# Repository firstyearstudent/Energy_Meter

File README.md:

<<<<<<< HEAD
# Energy_Meter
=======
# _Sample project_

(See the README.md file in the upper level 'examples' directory for more information about examples.)

This is the simplest buildable example. The example is used by command `idf.py create-project`
that copies the project to user specified path and set it's name. For more information follow the [docs page](https://docs.espressif.com/projects/esp-idf/en/latest/api-guides/build-system.html#start-a-new-project)

## How to use example
We encourage the users to use the example as a template for the new projects.
A recommended way is to follow the instructions on a [docs page](https://docs.espressif.com/projects/esp-idf/en/latest/api-guides/build-system.html#start-a-new-project).

## Example folder contents

The project **sample_project** contains one source file in C language [main.c](main/main.c). The file is located in folder [main](main).

ESP-IDF projects are built using CMake. The project build configuration is contained in `CMakeLists.txt`
files that provide set of directives and instructions describing the project's source files and targets
(executable, library, or both). 

Below is short explanation of remaining files in the project folder.

```
├── CMakeLists.txt
├── main
│   ├── CMakeLists.txt
│   └── main.c
└── README.md                  This is the file you are currently reading
```
Additionally, the sample project contains Makefile and component.mk files, used for the legacy Make based build system. 
They are not used or needed when building with CMake and idf.py.
>>>>>>> 912d5ab (first commit)

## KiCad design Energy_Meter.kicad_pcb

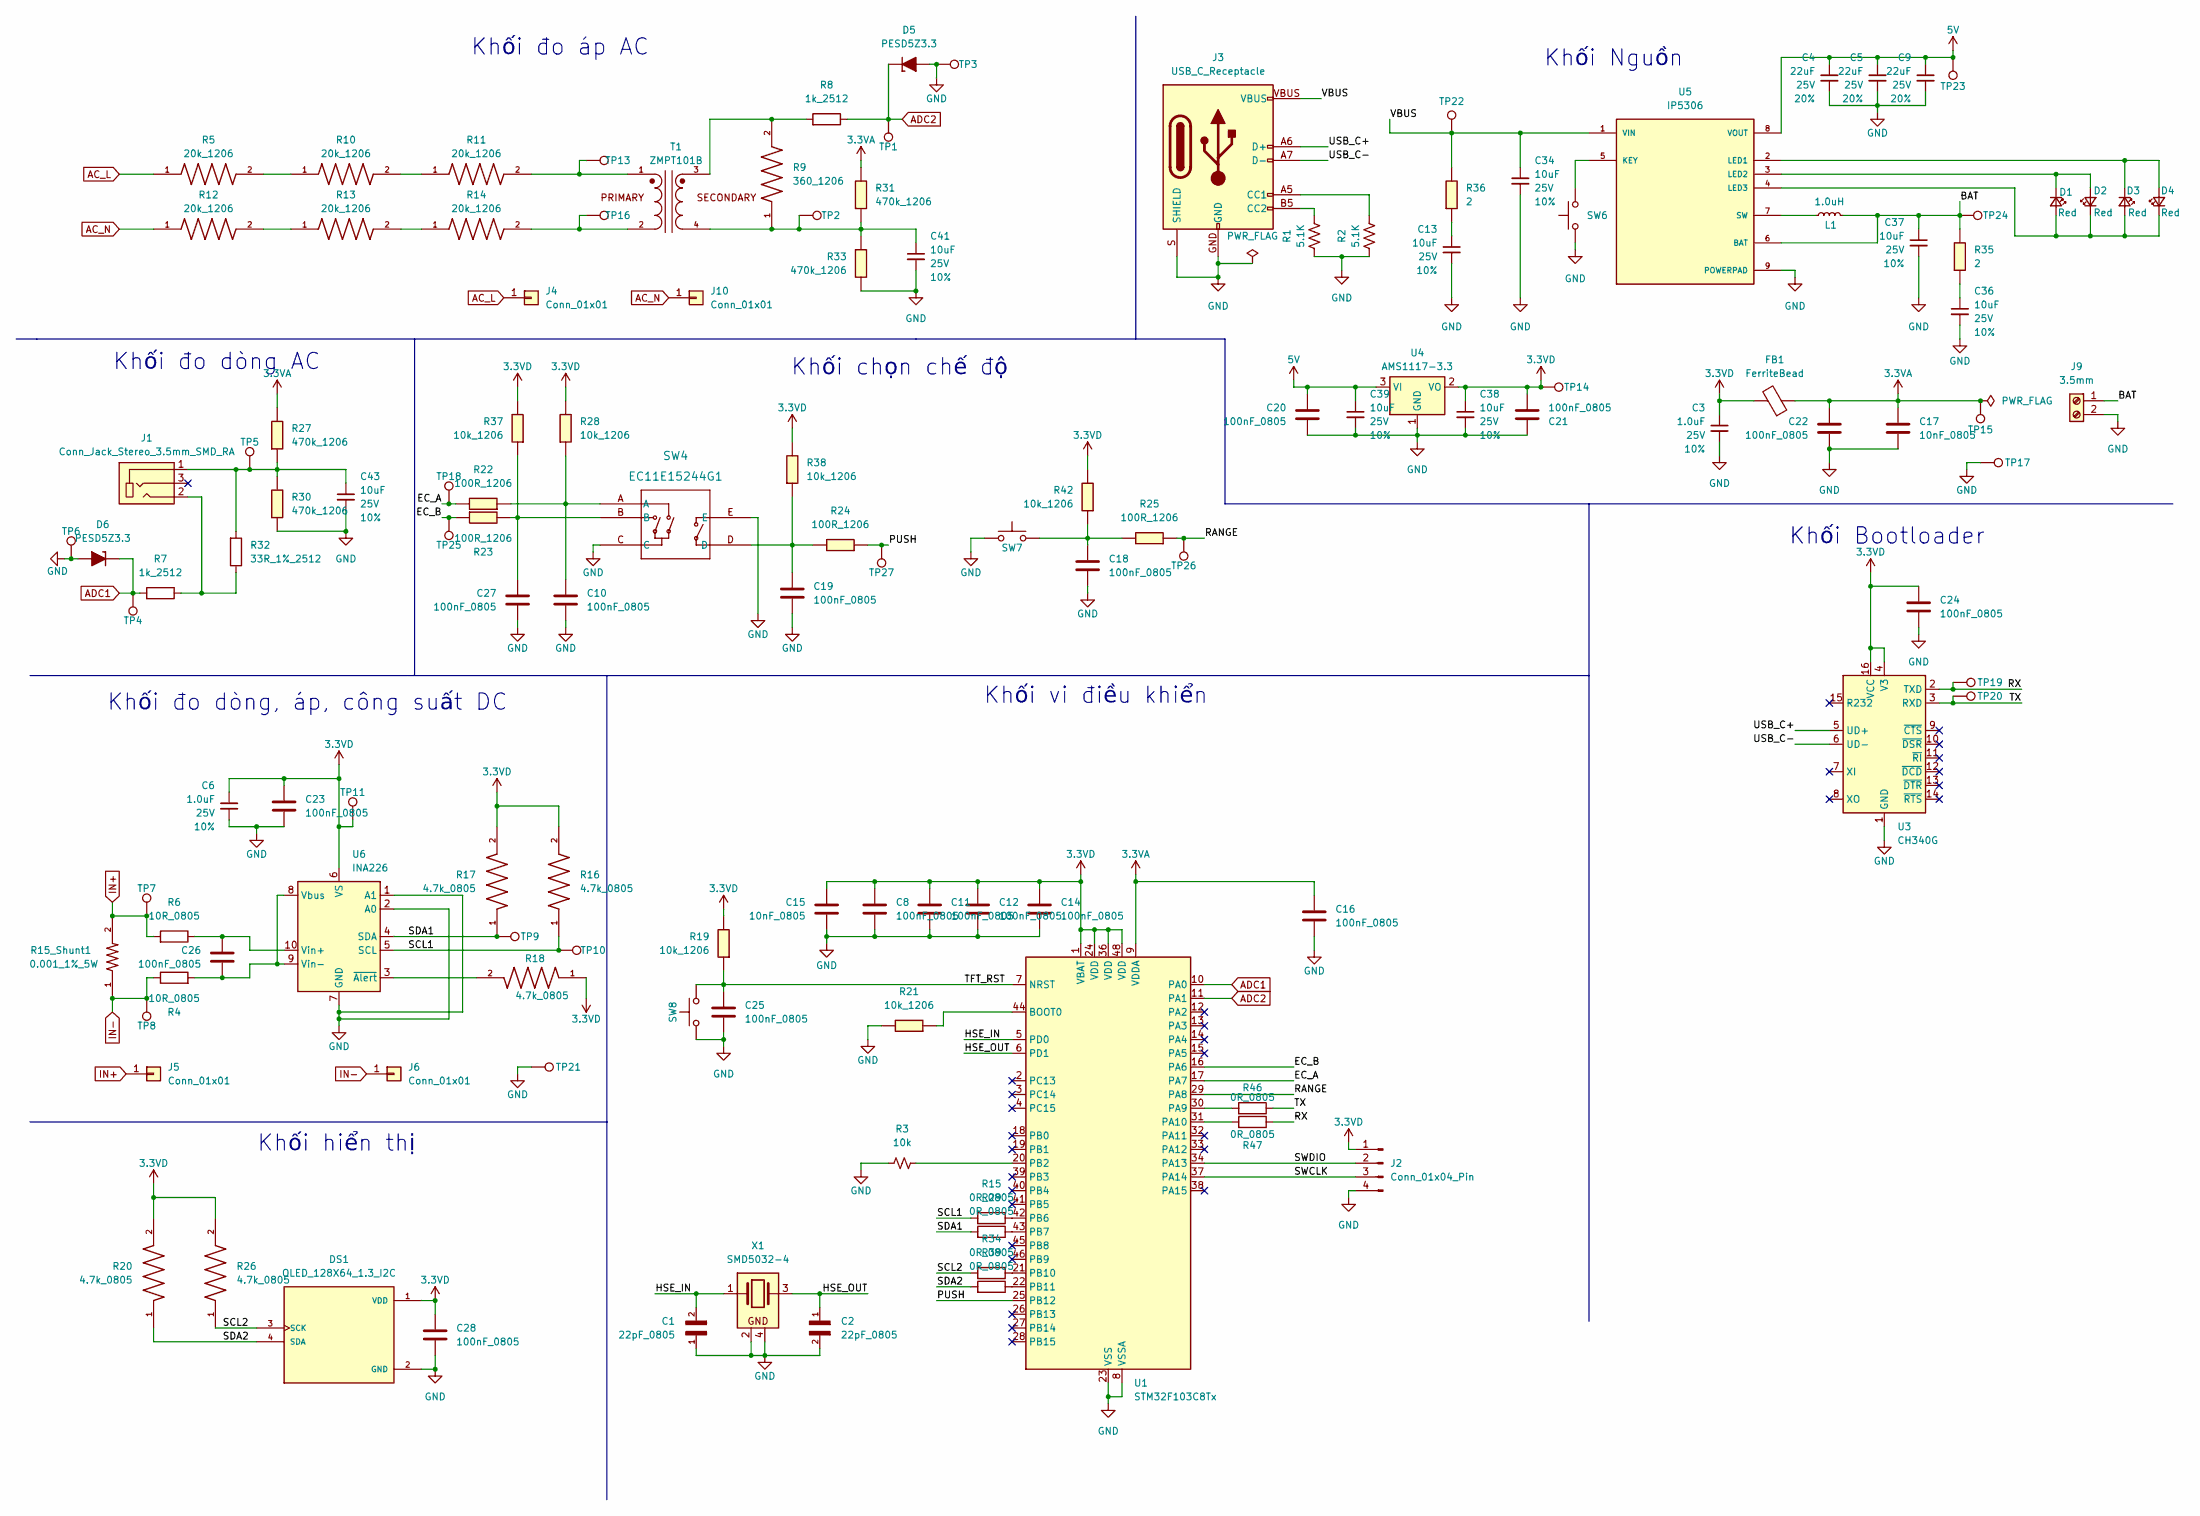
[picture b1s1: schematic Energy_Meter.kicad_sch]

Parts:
C1, C2: 22pF_0805; CAPC2012X88N
C3, C6: 1.0uF; C_0805_2012Metric; Voltage 25V; Tolerance 10%
C4, C5, C9: 22uF; C_0805_2012Metric; Voltage 25V; Tolerance 20%
C8, C10, C11, C12, C14, C16, C18, C19, C20, C21, C22, C23, C24, C25, C26, C27, C28: 100nF_0805; C_0805_2012Metric
C13, C34, C36, C37, C38, C39, C41, C43: 10uF; C_0805_2012Metric; Voltage 25V; Tolerance 10%
C15, C17: 10nF_0805; C_0805_2012Metric
D1, D2, D3, D4: Red; LED_1206_3216Metric_Red
D5, D6: PESD5Z3.3; D_SOD-523
DS1: OLED_128X64_1.3_I2C; LCD_OLED_128X64_1.3_I2C; PARTREV NA
FB1: FerriteBead; Ferrite_0805_2012Metric
J1: Conn_Jack_Stereo_3.5mm_SMD_RA; Conn_Jack_Stereo_3.5mm_CUI_SJ-3523-SMT-TR
J2: Conn_01x04_Pin; PinHeader_1x04_P2.54mm_Horizontal
J3: USB_C_Receptacle; USB-C_16
J4, J5, J6, J10: Conn_01x01; MountingHole_4.5mm_Pad
J9: 3.5mm; ScrewTerminal_1x02_P3.5mm_Horizontal_Black
L1: 1.0uH; 0805
R1, R2: 5.1K; R_1206_3216Metric; Part Number ERJ-8GEYJ512V
R3: 10k; R_0603_1608Metric
R4, R6: 10R_0805; R_0805_2012Metric
R5, R10, R11, R12, R13, R14: 20k_1206; RES_ERA8ARB203V; PARTREV 3/1/2020
R7, R8: 1k_2512; R_2512_6332Metric
R9: 360_1206; RESC3116X65N
R15, R29, R34, R39, R46, R47: 0R_0805; R_0805_2012Metric
R15_Shunt1: 0.001_1%_5W; RESC6331X88N
R16, R17, R18, R20, R26: 4.7k_0805; RESC2012X60N
R19, R21, R28, R37, R38, R42: 10k_1206; R_1206
R22, R23, R24, R25: 100R_1206; R_1206
R27, R30, R31, R33: 470k_1206; R_1206
R32: 33R_1%_2512; R_2512_6332Metric
R35, R36: 2; R_1206
SW4: EC11E15244G1; EC11E15244G1_AAL
SW6, SW7, SW8: SW_Push; SW_Tactile_SPST_NO_Straight_CK_PTS636Sx25SMTRLFS; Part Number PTS636 SK25 SMTR LFS
T1: ZMPT101B; XFMR_ZMPT101B; PARTREV NA
TP1, TP2, TP3, TP4, TP5, TP6, TP7, TP8, TP9, TP10, TP11, TP13, TP14, TP15, TP16, TP17, TP18, TP19, TP20, TP21, TP22, TP23, TP24, TP25, TP26, TP27: 0.5mm; TestPoint-0.5mm
U1: STM32F103C8Tx; LQFP-48_7x7mm_P0.5mm; Part Number STM32F103C8T6TR
U3: CH340G; SOIC-16_3.9x9.9mm_P1.27mm
U4: AMS1117-3.3; SOT-223-3_TabPin2; Part Number AMS1117-3.3
U5: IP5306; SOP127P600X165-9N; PARTREV 1.31
U6: INA226; TSSOP-10_3x3mm_P0.5mm
X1: SMD5032-4; Crystal_SMD_5032-4Pin_5.0x3.2mm

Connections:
3.3VA: C16.1, C17.1, C22.1, FB1.1, R27.1, R31.1, TP15.1 (1_1), U1.9 (VDDA)
3.3VD: C3.1, C6.1, C8.1, C11.1, C12.1, C14.1, C15.1, C21.2, C23.1, C24.1, C28.1, C38.1, DS1.1 (VDD), FB1.2, J2.1, R16.2, R17.2, R18.1, R19.1, R20.2, R26.2, R28.1, R37.1, R38.1, R42.1, TP11.1 (1_1), TP14.1 (1_1), U1.1 (VBAT), U1.24 (VDD), U1.36 (VDD), U1.48 (VDD), U3.4 (V3), U3.16 (VCC), U4.2 (VO), U6.6 (VS)
5V: C4.1, C5.1, C9.1, C20.1, C39.1, TP23.1 (1_1), U4.3 (VI), U5.8 (VOUT)
/BAT: C37.1, J9.1, L1.2, R35.1, TP24.1 (1_1), U5.6 (BAT)
/EC_A: R22.1, TP18.1 (1_1), U1.17 (PA7)
/EC_B: R23.2, TP25.1 (1_1), U1.16 (PA6)
/HSE_IN: C1.2, U1.5 (PD0), X1.1
/HSE_OUT: C2.1, U1.6 (PD1), X1.3
/PUSH: R24.2, TP27.1 (1_1), U1.25 (PB12)
/RANGE: R25.2, TP26.1 (1_1), U1.29 (PA8)
/RX: R47.2, TP19.1 (1_1), U3.2 (TXD)
/SCL1: R15.1, R16.1, TP10.1 (1_1), U6.5 (SCL)
/SCL2: DS1.3 (SCK), R26.1, R34.1
/SDA1: R17.1, R29.1, TP9.1 (1_1), U6.4 (SDA)
/SDA2: DS1.4 (SDA), R20.1, R39.1
/SWCLK: J2.3, U1.37 (PA14)
/SWDIO: J2.2, U1.34 (PA13)
/TFT_RST: C25.1, R19.2, SW8.2, U1.7 (NRST)
/TX: R46.2, TP20.1 (1_1), U3.3 (RXD)
/USB_C+: J3.A6 (D+), J3.B6 (D+), U3.5 (UD+)
/USB_C-: J3.A7 (D-), J3.B7 (D-), U3.6 (UD-)
/VBUS: C34.1, J3.VBUS, R36.1, TP22.1 (1_1), U5.1 (VIN)
AC_L: J4.1 (Pin_1_1), R5.1
AC_N: J10.1 (Pin_1_1), R12.1
ADC1: D6.1 (K), R7.1, TP4.1 (1_1), U1.10 (PA0)
ADC2: D5.1 (K), R8.2, TP1.1 (1_1), U1.11 (PA1)
GND: C1.1, C2.2, C3.2, C4.2, C5.2, C6.2, C8.2, C9.2, C10.2, C11.2, C12.2, C13.2, C14.2, C15.2, C16.2, C17.2, C18.2, C19.2, C20.2, C21.1, C22.2, C23.2, C24.2, C25.2, C27.2, C28.2, C34.2, C36.2, C37.2, C38.2, C39.2, C41.2, C43.2, D5.2 (A), D6.2 (A), DS1.2 (GND), J2.4, J3.GND, J3.S (SHIELD), J9.2, R1.1, R2.1, R3.1, R21.1, R30.2, R33.1, SW4.C, SW4.E, SW6.1, SW7.1, SW8.1, TP3.1 (1_1), TP6.1 (1_1), TP17.1 (1_1), TP21.1 (1_1), U1.8 (VSSA), U1.23 (VSS), U1.35 (VSS), U1.47 (VSS), U3.1 (GND), U4.1 (GND), U5.9 (POWERPAD), U6.1 (A1), U6.2 (A0), U6.7 (GND), X1.2, X1.4
IN+: J5.1 (Pin_1_1), R6.1, R15_Shunt1.2, TP7.1 (1_1)
IN-: J6.1 (Pin_1_1), R4.2, R15_Shunt1.1, TP8.1 (1_1)
unnamed: C10.1, R22.2, R28.2, SW4.A
unnamed: C13.1, R36.2
unnamed: C18.1, R25.1, R42.2, SW7.2
unnamed: C19.1, R24.1, R38.2, SW4.D
unnamed: C27.1, R23.1, R37.2, SW4.B
unnamed: C36.1, R35.2
unnamed: C41.1, R9.1, R31.2, R33.2, T1.4, TP2.1 (1_1)
unnamed: C43.1, J1.1, R27.2, R30.1, R32.1, TP5.1 (1_1)
unnamed: D1.2 (A), D2.1 (K), D3.2 (A), D4.1 (K), U5.4 (LED3)
unnamed: D1.1 (K), D2.2 (A), U5.3 (LED2)
unnamed: D3.1 (K), D4.2 (A), U5.2 (LED1)
unnamed: J1.2, R7.2, R32.2
unnamed: J3.A5 (CC1), R2.2
unnamed: J3.B5 (CC2), R1.2
unnamed: R8.1, R9.2, T1.3
unnamed: R5.2, R10.1
unnamed: R10.2, R11.1
unnamed: R11.2, T1.1, TP13.1 (1_1)
unnamed: R12.2, R13.1
unnamed: R13.2, R14.1
unnamed: R14.2, T1.2, TP16.1 (1_1)
unnamed: R21.2, U1.44 (BOOT0)
unnamed: R46.1, U1.30 (PA9)
unnamed: R47.1, U1.31 (PA10)
unnamed: R3.2, U1.20 (PB2)
unnamed: R15.2, U1.42 (PB6)
unnamed: R29.2, U1.43 (PB7)
unnamed: R34.2, U1.21 (PB10)
unnamed: R39.2, U1.22 (PB11)
unnamed: SW6.2, U5.5 (KEY)
unnamed: L1.1, U5.7 (SW)
unnamed: C26.2, R4.1, U6.8 (Vbus), U6.9 (Vin-)
unnamed: C26.1, R6.2, U6.10 (Vin+)
unnamed: R18.2, U6.3 (~Alert)

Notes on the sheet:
Khối Nguồn
Khối đo dòng AC
Khối chọn chế độ
Khối hiển thị
Khối Bootloader
Khối vi điều khiển
Khối đo áp AC
Khối đo dòng, áp, công suất DC

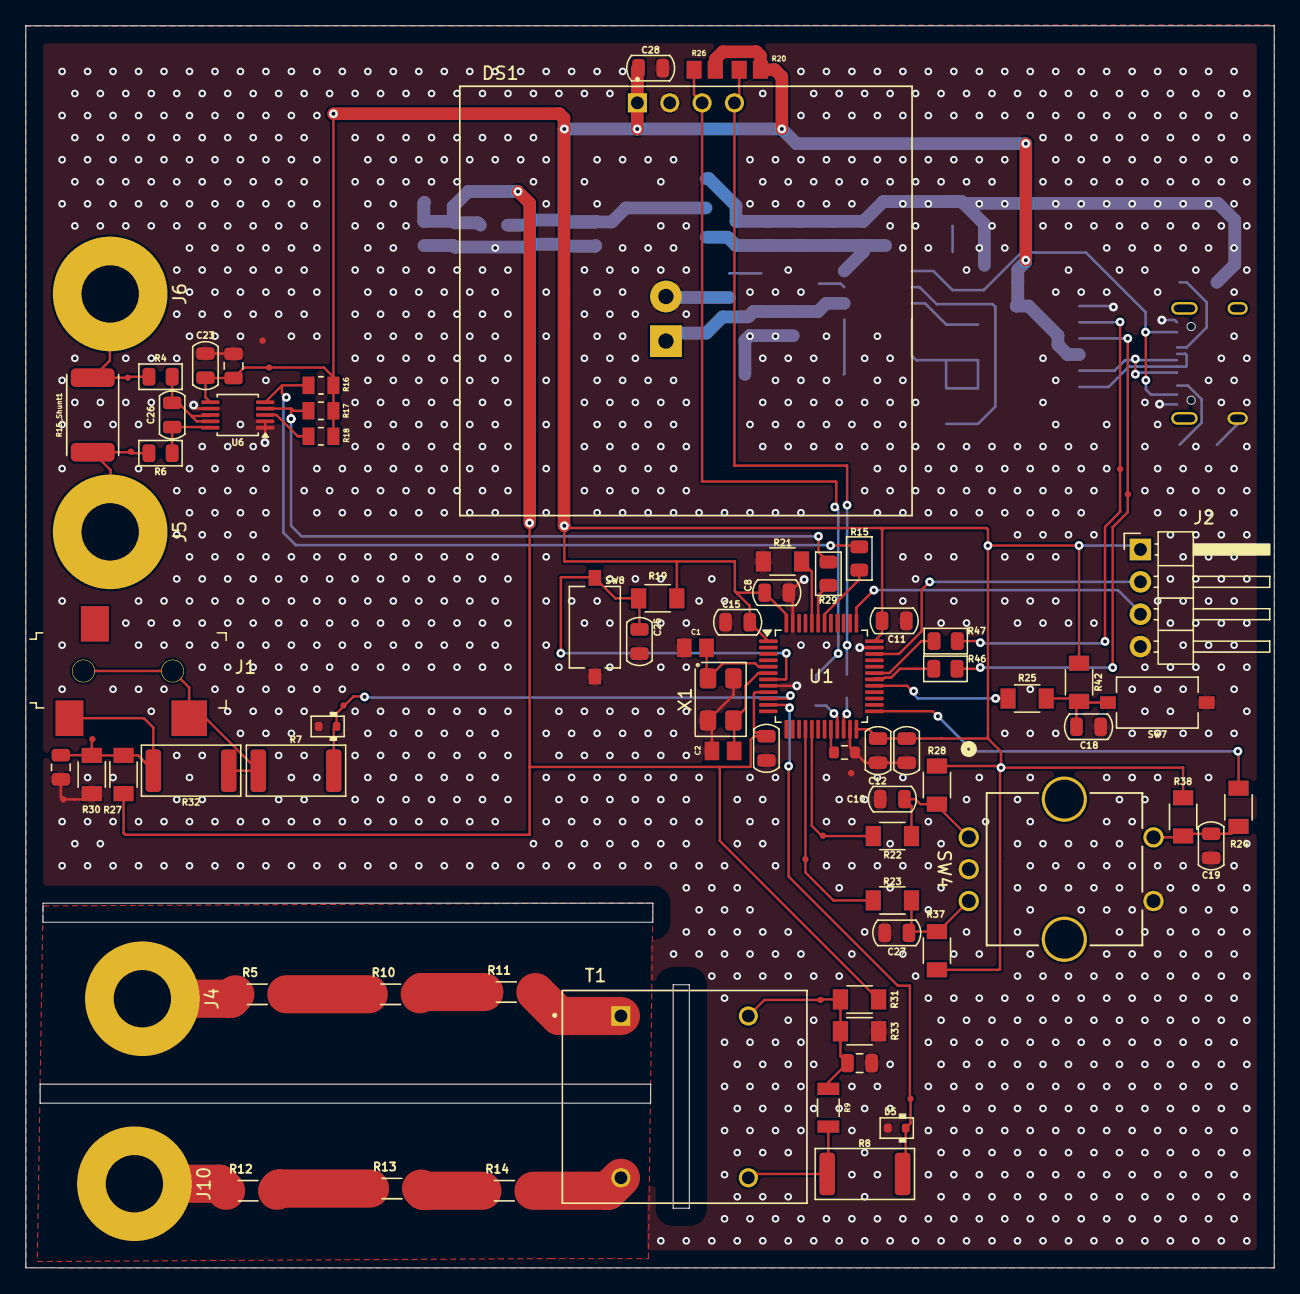
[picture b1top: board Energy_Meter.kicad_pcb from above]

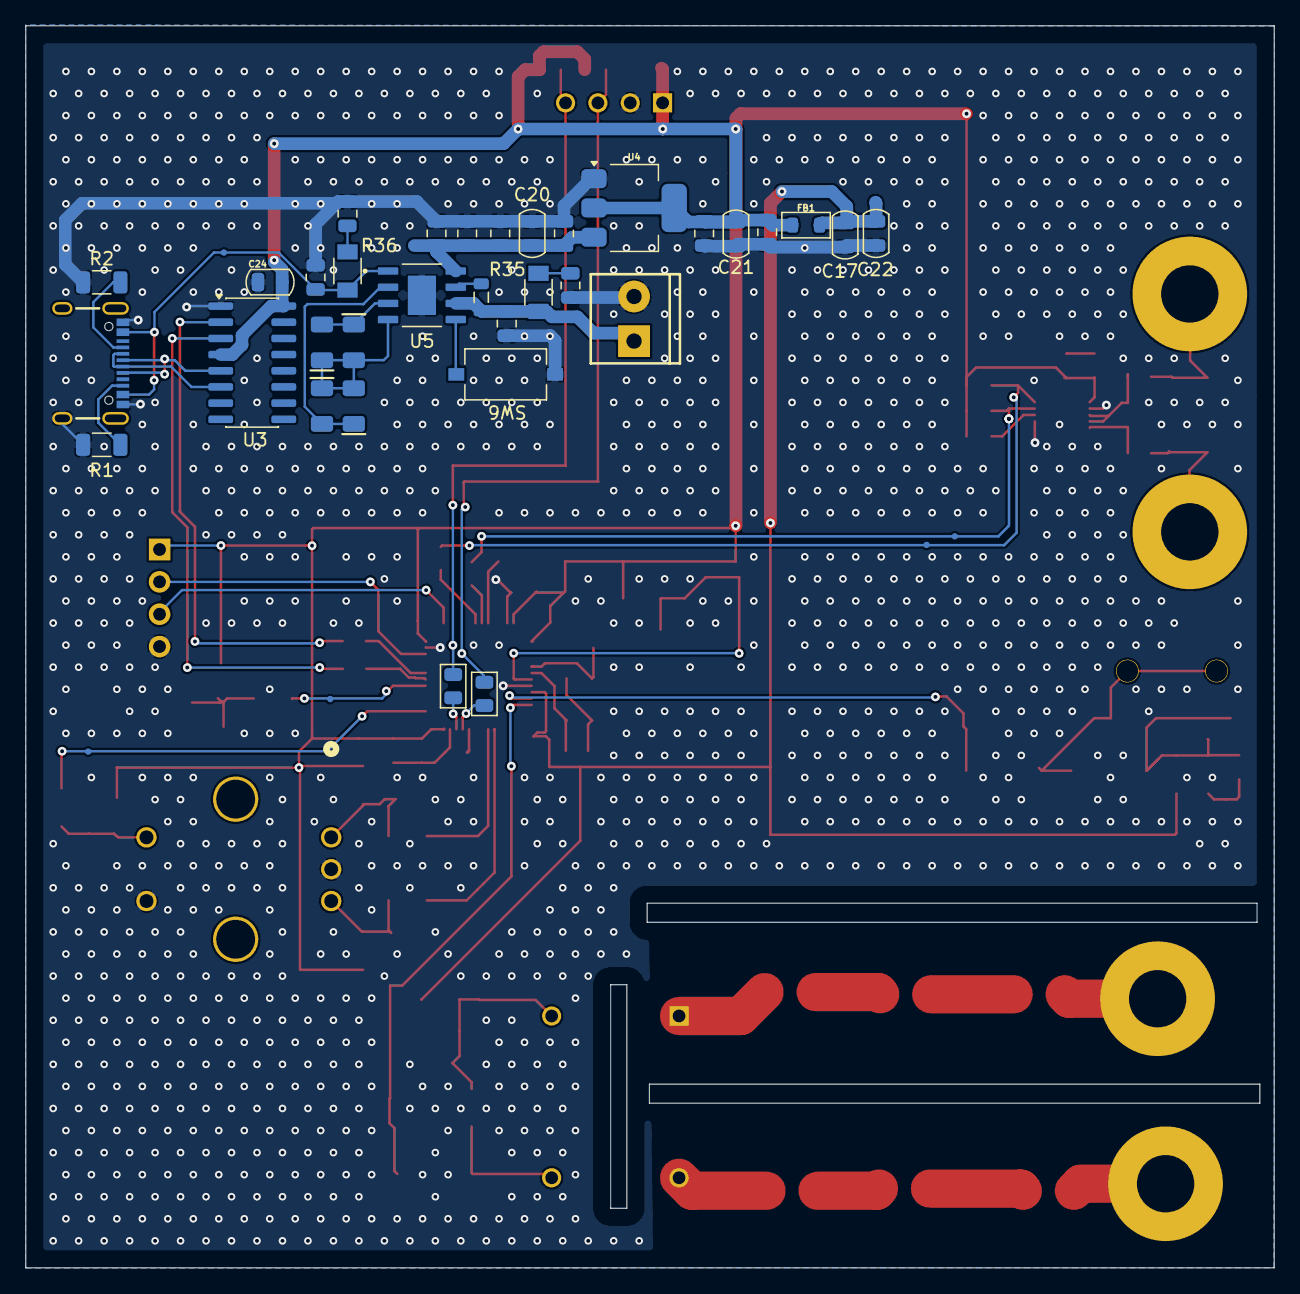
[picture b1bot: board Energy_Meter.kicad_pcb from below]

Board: 2 copper layers, 98.0 x 97.5 mm, 131 parts (42 on the bottom side), 63 nets.

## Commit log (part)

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2026-06-15 update 15/06/2026
2026-06-18 update 18/06/2026
2026-06-19 update 19/06/2026
2026-06-23 update 23/06/2026
2026-06-24 update 24/06/2026
2026-06-26 update 26/06/2026
2026-06-30 update 30/06/2026
